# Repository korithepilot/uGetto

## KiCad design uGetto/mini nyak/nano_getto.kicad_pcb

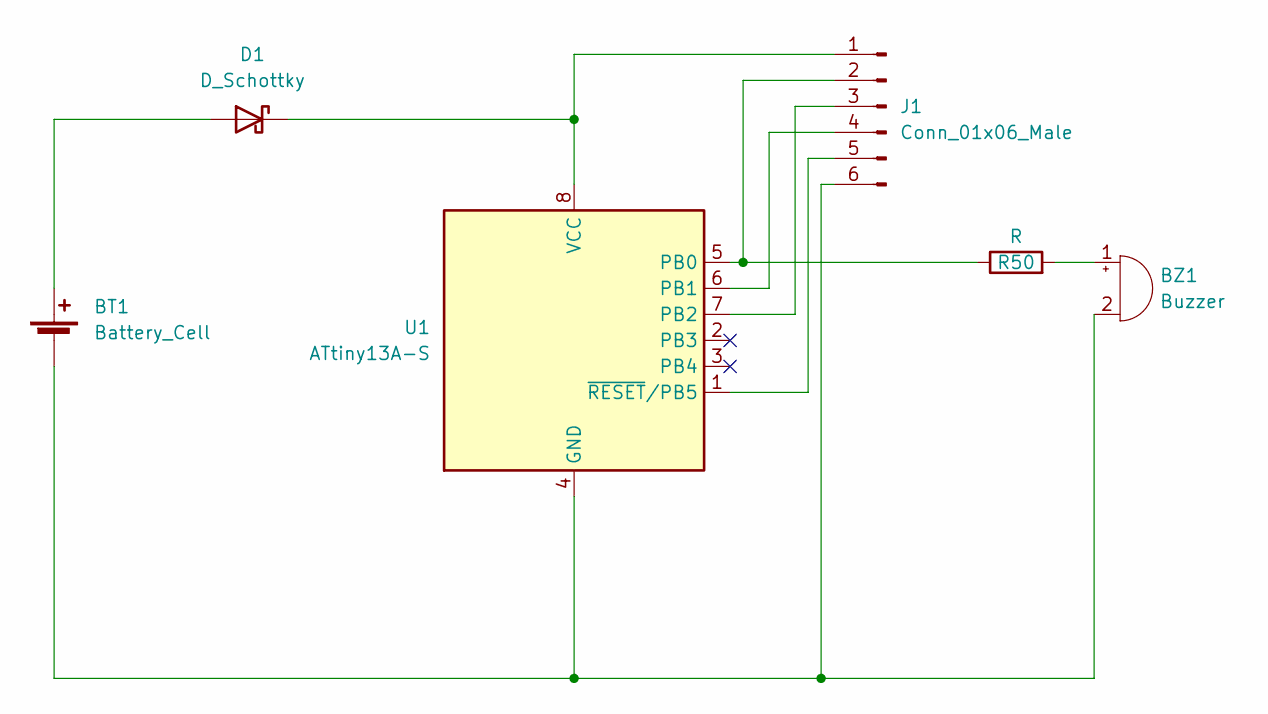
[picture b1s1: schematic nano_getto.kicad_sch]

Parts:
BT1: Battery_Cell; BatteryHolder_Keystone_103_1x20mm
BZ1: Buzzer; HPM14A
D1: D_Schottky; D_5W_P10.16mm_Horizontal
J1: Conn_01x06_Male; PinHeader_1x06_P2.54mm_Vertical
R50: R; R_0805_2012Metric_Pad1.20x1.40mm_HandSolder
U1: ATtiny13A-S; SOIC-8W_5.3x5.3mm_P1.27mm

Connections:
unnamed: BT1.1 (+), D1.2 (A)
unnamed: BT1.2 (-), BZ1.2 (+), J1.6, U1.4 (GND)
unnamed: BZ1.1 (-), R50.2
unnamed: D1.1 (K), J1.1, U1.8 (VCC)
unnamed: J1.2, R50.1, U1.5 (PB0)
unnamed: J1.3, U1.7 (PB2)
unnamed: J1.4, U1.6 (PB1)
unnamed: J1.5, U1.1 (~RESET/PB5)

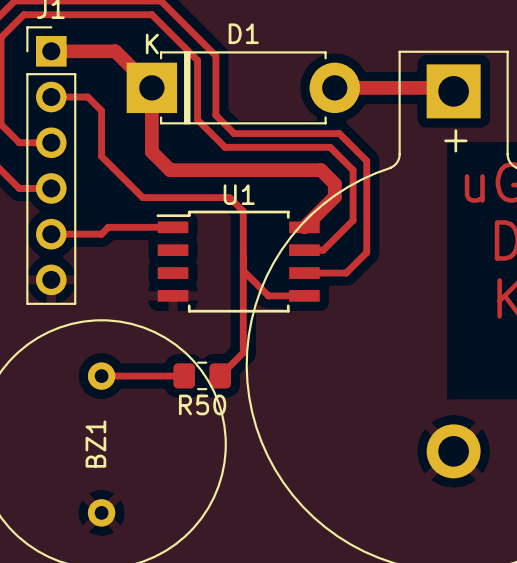
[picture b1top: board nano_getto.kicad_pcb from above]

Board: 2 copper layers, 6 parts (0 on the bottom side), 8 nets.

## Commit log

2022-09-14 Changed attiny13a footprint to SOIC8W
2022-09-15 first code making sound
2022-09-15 not tested generic melody player implementation
2022-09-15 now with Rick Astley™
2022-09-15 fixed #define
2022-09-15 actually working rickroll
2022-09-16 just the essential parts
2022-09-16 Button and led
2022-09-16 test
